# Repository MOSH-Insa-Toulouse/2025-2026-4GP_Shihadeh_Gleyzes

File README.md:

#  Projet : Du capteur au banc de test - Jauge de contrainte en graphite

L'objectif principal de ce projet est d'évaluer une technologie "low-tech" : un capteur de déformation (jauge de contrainte) fabriqué à partir de graphite. Pour cela, nous avons conçu de A à Z une chaîne de mesure complète, allant de la physique du capteur jusqu'à l'application smartphone, en passant par le conditionnement électronique et la création d'un banc de test automatisé.

##  Équipe Projet
* **[Jules Gleyzes]**  **[Samy Shihadeh]**
* Année : 2025-2026

---

##  Sommaire des livrables
1. [Le Capteur en Graphite](#1-le-capteur-en-graphite-low-tech)
2. [Électronique Analogique et Simulation (LTspice)](#2-électronique-analogique-et-simulation-ltspice)
3. [Le Shield PCB (KiCad)](#3-le-shield-pcb-kicad)
4. [Le Code Arduino](#4-programmation-arduino)
5. [L'Application Android](#5-application-android)
6. [Le Banc de Test](#6-le-banc-de-test)
7. [La Datasheet Finale](#7-datasheet-du-capteur)
8. [Conclusion](#8-conclusion)

---

## 1. Le Capteur en Graphite (Low-Tech)
Notre jauge de contrainte a été fabriquée selon une approche "low-tech", en crayonnant simplement une zone spécifique sur une feuille de papier avec un crayon à papier (graphite). Derrière cette apparente simplicité se cache en réalité un capteur régi par la mécanique quantique. 
### 1.1. Géométrie et Fabrication 
**Support :** Papier classique.  **Matériau sensible :** Dépôt de graphite par frottement.  **Dimensions :** Motif en forme de "U" avec une longueur de bande de 35 mm et un espacement de 5 mm.

### 1.2. Principe Physique : 
Réseau de percolation et Effet Tunnel. Les traits de crayon déposés sur du papier forme un **réseau de percolation** : un grand nombre de micro et nano-grains de graphite dispersées de façon aléatoire. Pour que le courant traverse le capteur, les électrons utilisent deux mécanismes : 1. **La conduction ohmique :** Lorsque les grains se touchent physiquement. 2. **L'effet tunnel quantique :** Lorsque deux grains sont séparées par un vide ou un isolant nanométrique, les électrons (qui se comportent comme des ondes) ont une probabilité de "traverser" cette barrière. La résistance électrique liée à cet effet tunnel R_tunnel dépend de manière **exponentielle** de la distance d entre les grains de graphite.
### 1.3. Réponse à la déformation (Macroscopique) 
C'est cette sensibilité exponentielle à la distance nanométrique qui permet au capteur de mesurer une déformation mécanique. **En Tension (étirement / courbure vers l'extérieur) :** Les fibres du papier s'étirent, éloignant les grains de graphite les unes des autres. La distance d des jonctions augmente. L'effet tunnel ne fonctionne plus, ce qui **augmente fortement la résistance électrique globale**. **En Compression (courbure vers l'intérieur) :** Les fibres du papier se resserent. Les grains sont rapprochées, créant de nouveaux contacts physiques et diminuant la distance d des jonctions tunnel. Les électrons circulent beaucoup plus facilement, ce qui **diminue la résistance électrique**. Ce capteur low-tech est donc un détecteur quantique de variations de distances nanométriques.
## 2. Électronique Analogique et Simulation (LTspice)

Avant de passer à la réalisation physique sur notre shield, il est important de valider le comportement de notre signal de manière théorique. Nous avons utilisé le logiciel LTspice pour modéliser le circuit complet afin d'ajuster la valeur de nos composants et vérifier la réponse du système. Notre capteur en graphite possède une résistance électrique très élevée, il ne laisse donc passer qu'un courant de l'ordre du microampère. La carte Arduino ne lisant que des tensions (de 0 à 5V), une amplification du signal est donc essentiel.

### 2.1. Amplification Transimpédance et Étalonnage Dynamique

Le cœur de notre circuit repose sur un amplificateur opérationnel monté en transimpédance. Ce montage force le très faible courant du capteur à traverser la résistance de rétroaction R4 (100 kΩ) pour générer une tension de sortie que l’arduino est capable de lire. 

### 2.2. Filtrage des Parasites Ambiants

Le graphite et les fils de connexion apportent des signaux parasites à cause des ondes ambiantes. Pour obtenir une mesure propre et exploitable, nous avons étagé deux filtres. 

Le premier est un filtre actif formé par le condensateur C2 (1 µF) placé en parallèle de R4. Il crée un filtre passe-bas du premier ordre dont la fréquence de coupure est calculée par la formule f_c = 1/(2pi*R4*C2), ce qui donne environ 1.6 Hz. Cela bloque le bruit à 50 Hz tout en laissant passer les variations lentes correspondant à nos contraintes mécaniques. Enfin, un second filtre passe-bas, passif cette fois, est placé juste avant la broche de lecture de l'Arduino. Composé de R3 (1 kΩ) et C3 (100 nF), il possède une fréquence de coupure d'environ 1.6 kHz pour supprimer les bruits à très haute fréquence.

 **

## 3. Le Shield PCB (KiCad)
 Pour intégrer proprement notre circuit au microcontrôleur, nous avons conçu un "Shield" sur mesure à l'aide du logiciel **KiCad**. Le principe d'un shield est d'être une carte d'extension conçue pour se connecter directement par-dessus la carte Arduino UNO. Cette approche permet de supprimer le câblage pour avoir un tout plus compact et un visuel moins encombré. 
### Les Composants Intégrés 
Notre carte comprend un ensemble d’éléments matériels nécessaires au fonctionnement du système : 
* **Le capteur en graphite **
* **Le circuit d'amplification transimpédance :** Converti le micro-courant du capteur en une tension (0-5V) lisible par la carte arduino et de filtre les bruits parasites. 
* **Le potentiomètre :** Intégré au circuit d'amplification et piloté par la carte, il sert à étalonner le signal. Il adapte le gain en temps réel pour garantir une lecture précise, peu importe la résistance du capteur fabriqué.
* **L'écran OLED :** L'interface visuelle qui permet de lire les mesures en direct et de visualiser les différents menus de la carte. 
* **L'encodeur rotatif :** Molette cliquable permettant à l'utilisateur de naviguer dans les menus de l'écran et de déclencher les mesures. 
* **Le module Bluetooth :** Transmet les données traitées en temps réel vers notre application smartphone Android. 

### De la Conception à la Réalisation 
Pour aboutir à notre carte physique, nous sommes passés par deux grandes étapes de conception sur KiCad : 
**1. Le Schématique Électrique** C'est ici que nous avons défini les liens logiques entre tous nos composants et le microcontrôleur, en utilisant des labels pour garder un document lisible.

**2. Le Routage (PCB)** Une fois le schéma validé, nous avons placé physiquement les composants sur une carte et tracé les pistes de cuivre (en respectant une largeur et une isolation de 0.5 mm minimum).

## 4. Programmation Arduino

Tous les composants de notre shield sont pilotés par une carte Arduino UNO. Le code est disponible dans ce dépôt.

Dès qu'on branche la carte, l'Arduino lance une **calibration automatique**. Le programme va tester rapidement plusieurs valeurs sur le potentiomètre numérique pour s'adapter tout seul à la résistance de votre capteur.

Ensuite, l'écran OLED affiche le menu principal. La navigation se fait très simplement avec l'encodeur rotatif : il suffit de tourner la molette pour faire défiler les menus, et de cliquer dessus pour y entrer.

Le programme propose deux menus :

* **Menu 1 : Mesure en direct** Affiche la résistance du capteur graphite en temps réel. Le code adapte tout seul l'unité (Ohms, kOhms ou MOhms). Pour que l'affichage soit agréable à lire et que les chiffres ne sautent pas dans tous les sens, nous avons ajouté un petit filtre dans le code qui fait une moyenne sur les 15 dernières mesures.

* **Menu 2 : Infos Créateurs**
Un petit menu de crédits qui affiche les informations de notre binôme (Samy Shihadeh & Jules Gleyzes - GP 4A 2026).

## 5. Application Android 

Pour visualiser les données de notre capteur sans avoir besoin d'un ordinateur, nous avons développé une petite application Android. Elle communique directement avec le module Bluetooth de notre carte.

Nous avons créé cette application en utilisant MIT App Inventor qui permet grâce à un système de programmation par blocs de développer rapidement une application fonctionnelle.

L'application a deux rôles principaux :
1. **La connexion :** Elle permet de chercher et de se connecter facilement au module Bluetooth.
3. **L'affichage :** Une fois connectée, elle reçoit les valeurs de résistance mesurées et les affiche sur l'écran du téléphone quand on appuie dessus.

**L'interface utilisateur :**

**Le code par blocs :**

## 6. Le Banc de Test

Pour valider scientifiquement l'efficacité de nos capteurs "low-tech" en graphite, il était indispensable de caractériser leur réponse face à des déformations mécaniques connues. 

Nous avons conçu un banc de test en utilisant une pièce imprimée en 3D en forme de cône. Celui-ci possède différents rayons de courbure de sorte que l’on puisse tordre nos différent de capteurs, fait à partir de différents types de graphite, de la même manière.

Afin d'évaluer et de comparer les performances de nos différents capteurs, nous avons étudié l'évolution de leur signal en fonction de la contrainte mécanique appliquée. Pour ce faire, nous avons tracé la variation relative de la résistance (R - R_0)/R_0 en fonction de la déformation. Avec R la résistance du capteur sous contrainte et R_0 la résistance du capteur lorsqu'il est à plat.

## 7. Datasheet du Capteur

Pour valider le fonctionnement du capteur, nous avons mesuré l'évolution de sa résistance relative (ΔR/R_0) en fonction de la déformation appliquée, en testant différentes duretés de mines de graphite. 

Bien que ces courbes valident le principe physique de base (la résistance augmente en extension et diminue en compression grâce à l'effet tunnel), elles mettent également en évidence les limites du capteur *low-tech* fabriqué à la main :

* **Non-linéarité et variabilité :** L'épaisseur du dépôt de graphite n'étant pas parfaitement uniforme lors d'un coloriage manuel, la réponse électrique présente des irrégularités selon les échantillons.
* **La limite de rupture mécanique :** Sur le graphique de compression, on observe une remontée anormale et soudaine de la résistance pour des déformations supérieures à 0,004. Cela peut s'expliquer par la nature du substrat : au-delà d'un certain angle, le papier ne fait plus que se courber, il peut se casser en marquant un pli. Cette pliure casse physiquement les chemins de percolation du graphite, faussant totalement la mesure.

## 8. Conclusion

Ce projet nous a permis de prouver qu'il est possible de créer un capteur de flexion fonctionnel avec un simple crayon à papier. 

Le comportement du capteur dépend directement de la composition de la mine, qui est un mélange de **graphite** (conducteur) et **d'argile** (isolant) :

* **Les mines grasses (ex: 3B) :** Riches en graphite, elles déposent une couche épaisse et très conductrice sur le papier.Le capteur est donc **stable et linéaire, mais moins sensible**.
* **Les mines dures (ex: 3H) :** Riches en argile (isolante) et pauvres en graphite, elles laissent un dépôt plus fin. À la moindre déformation, ce fragile réseau conducteur risque de se rompre partiellement. Le capteur devient alors **extrêmement sensible**, mais ses mesures sont plus difficiles à répéter.
On a pu voir que plus la mine du crayon est dure, plus le capteur réagit fort. Cependant, les mines classiques (HB, 2B) offrent des mesures plus stables.

### Peut-on industrialiser ce capteur ?
À grande échelle, **non**. Le principal problème est qu'il est impossible de colorier deux capteurs exactement de la même manière à la main. Les résultats sont donc trop variables pour l'industrie. De plus, les tests réalisés sur les capteur ont démontré leurs manque de duraibilité, les morceaux de papier se cassent après peu d'utilisations.

Précision après présentation :

La qualité de nos mesure ne permet pas de s'exprimer clairement sur la possibilité d'industrialiser ce capteur, cependant notre capteur a très basse compression ou extension démontre une sensibilité extremement bonne (par exemple nous avons presque une sensibilité de 100 pour le crayon B en compression) ce qui nous laisse a penser qu'après stabilisation des mesures avec des modifications apportées sur nos capteurs, ils pourraient avoir des caractéristiques interessantes d'un point de vu performance.

Une piste possible serait d'appliquer de la lacque ou encore de chauffer nos capteur avant test pour bien fixer le graphite sur notre feuille et refaire nos mesures pour déterminer si nos capteurs se comportent normalement.

De plus, son coût quasi nul et sa simplicité de fabrication en font un très bon outil éducatif qui permettent de découvrir tout les aspects nécessaire à prendre en compte et à étudier dans la création d'un capteur.

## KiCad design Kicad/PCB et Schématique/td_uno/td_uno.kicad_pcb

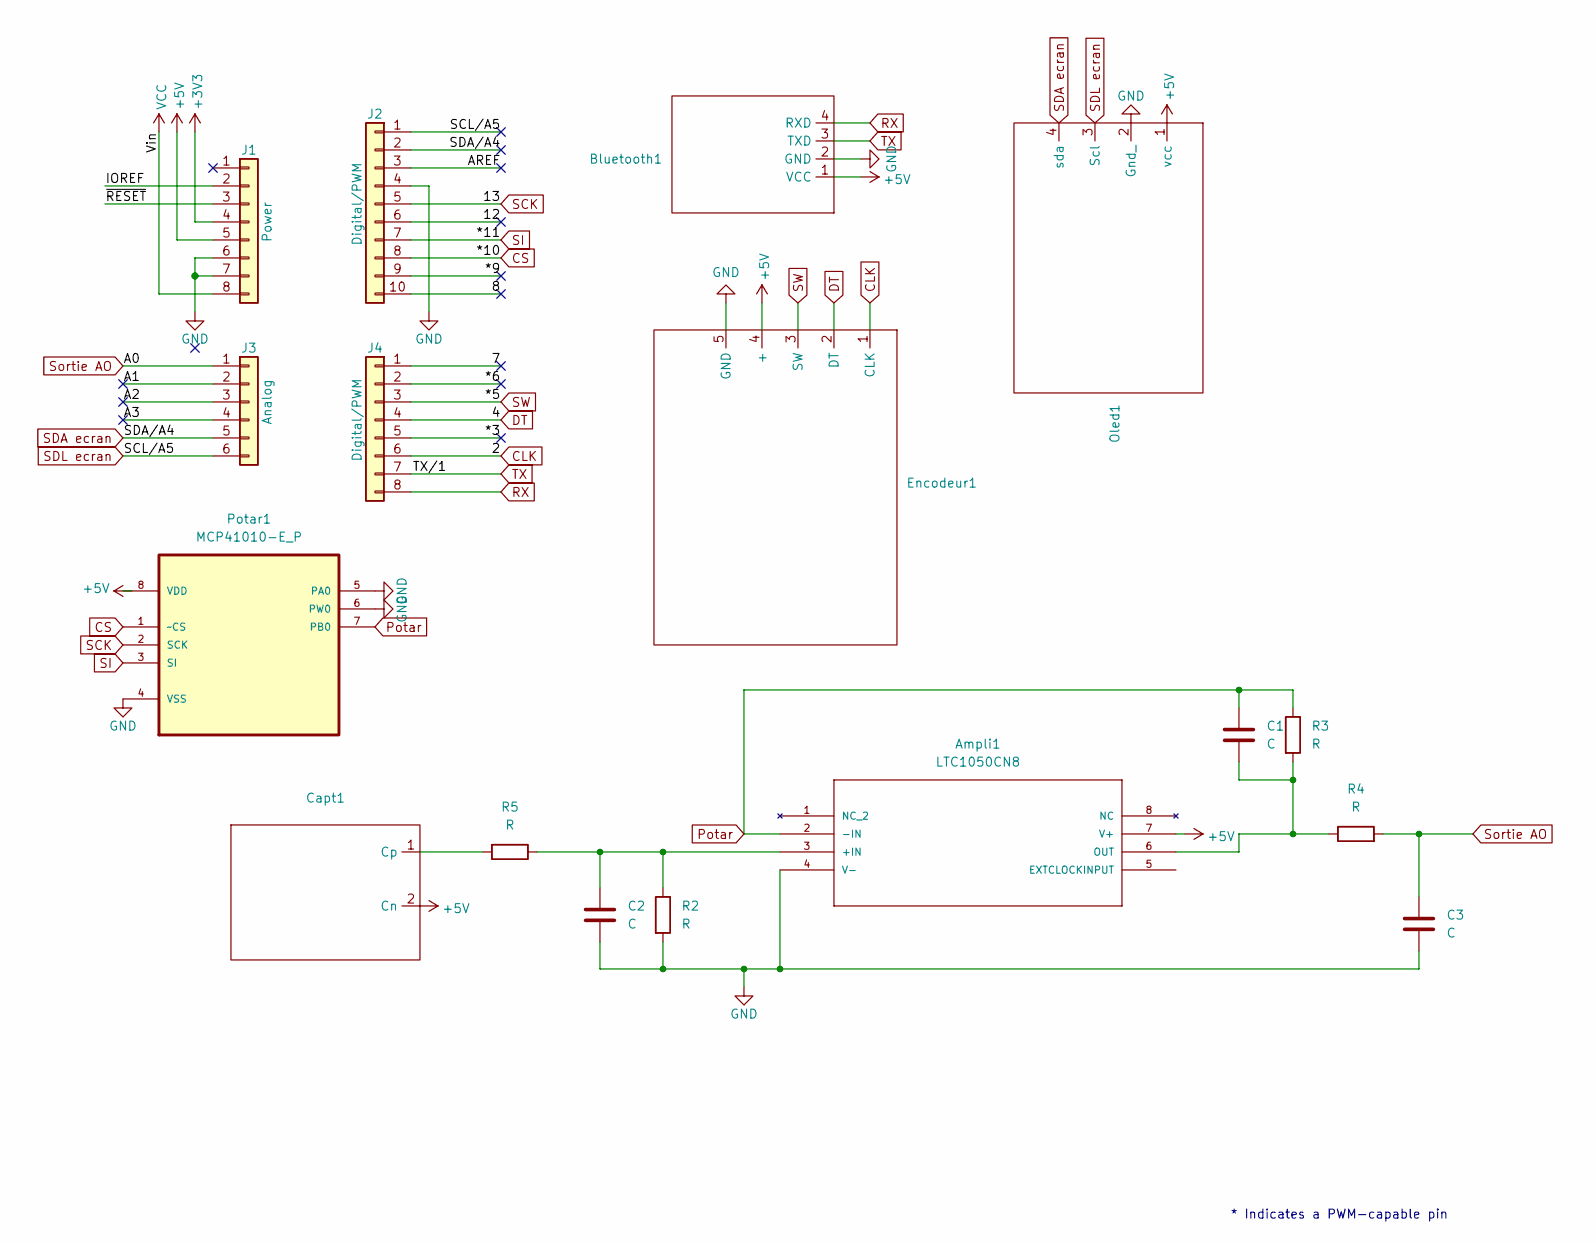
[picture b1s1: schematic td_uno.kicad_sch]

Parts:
Ampli1: LTC1050CN8; Ampli; MANUFACTURER_PART_NUMBER ltc1050cn8
Bluetooth1: Bluetooth
C1, C2, C3: C; C_Disc_D4.3mm_W1.9mm_P5.00mm
Capt1: Capt
Encodeur1: Encodeur
J1: Power; PinSocket_1x08_P2.54mm_Vertical
J2: Digital/PWM; PinSocket_1x10_P2.54mm_Vertical
J3: Analog; PinSocket_1x06_P2.54mm_Vertical
J4: Digital/PWM; PinSocket_1x08_P2.54mm_Vertical
Oled1: Oled
Potar1: MCP41010-E_P; Potar; MPN MCP41010-E/P; DigiKey_Part_Number MCP41010-E/P-ND
R2, R3, R4, R5: R; R_Axial_DIN0204_L3.6mm_D1.6mm_P5.08mm_Horizontal

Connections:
+3V3: J1.4
+5V: Ampli1.7 (V+), Bluetooth1.1 (VCC), Capt1.2 (Cn), Encodeur1.4 (+), J1.5, Oled1.1 (vcc), Potar1.8 (VDD)
/7: J4.1
/8: J2.10
/12: J2.6
/*3: J4.5
/*6: J4.2
/*9: J2.9
/A1: J3.2
/A2: J3.3
/A3: J3.4
/AREF: J2.3
/IOREF: J1.2
/~RESET: J1.3
CLK: Encodeur1.1 (CLK), J4.6
CS: J2.8, Potar1.1 (~CS)
DT: Encodeur1.2 (DT), J4.4
GND: Ampli1.4 (V-), Bluetooth1.2 (GND), C2.2, C3.2, Encodeur1.5 (GND), J1.6, J1.7, J2.4, Oled1.2 (Gnd_), Potar1.4 (VSS), Potar1.5 (PA0), Potar1.6 (PW0), R2.2
unnamed: Ampli1.3 (+IN), C2.1, R2.1, R5.1
unnamed: Ampli1.6 (OUT), C1.2, R3.2, R4.1
unnamed: Capt1.1 (Cp), R5.2
Potar: Ampli1.2 (-IN), C1.1, Potar1.7 (PB0), R3.1
RX: Bluetooth1.4 (RXD), J4.8
SCK: J2.5, Potar1.2 (SCK)
SDA ecran: J2.2, J3.5, Oled1.4 (sda)
SDL ecran: J2.1, J3.6, Oled1.3 (Scl)
SI: J2.7, Potar1.3 (SI)
SW: Encodeur1.3 (SW), J4.3
Sortie AO: C3.1, J3.1, R4.2
TX: Bluetooth1.3 (TXD), J4.7
VCC: J1.8

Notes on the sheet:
* Indicates a PWM-capable pin

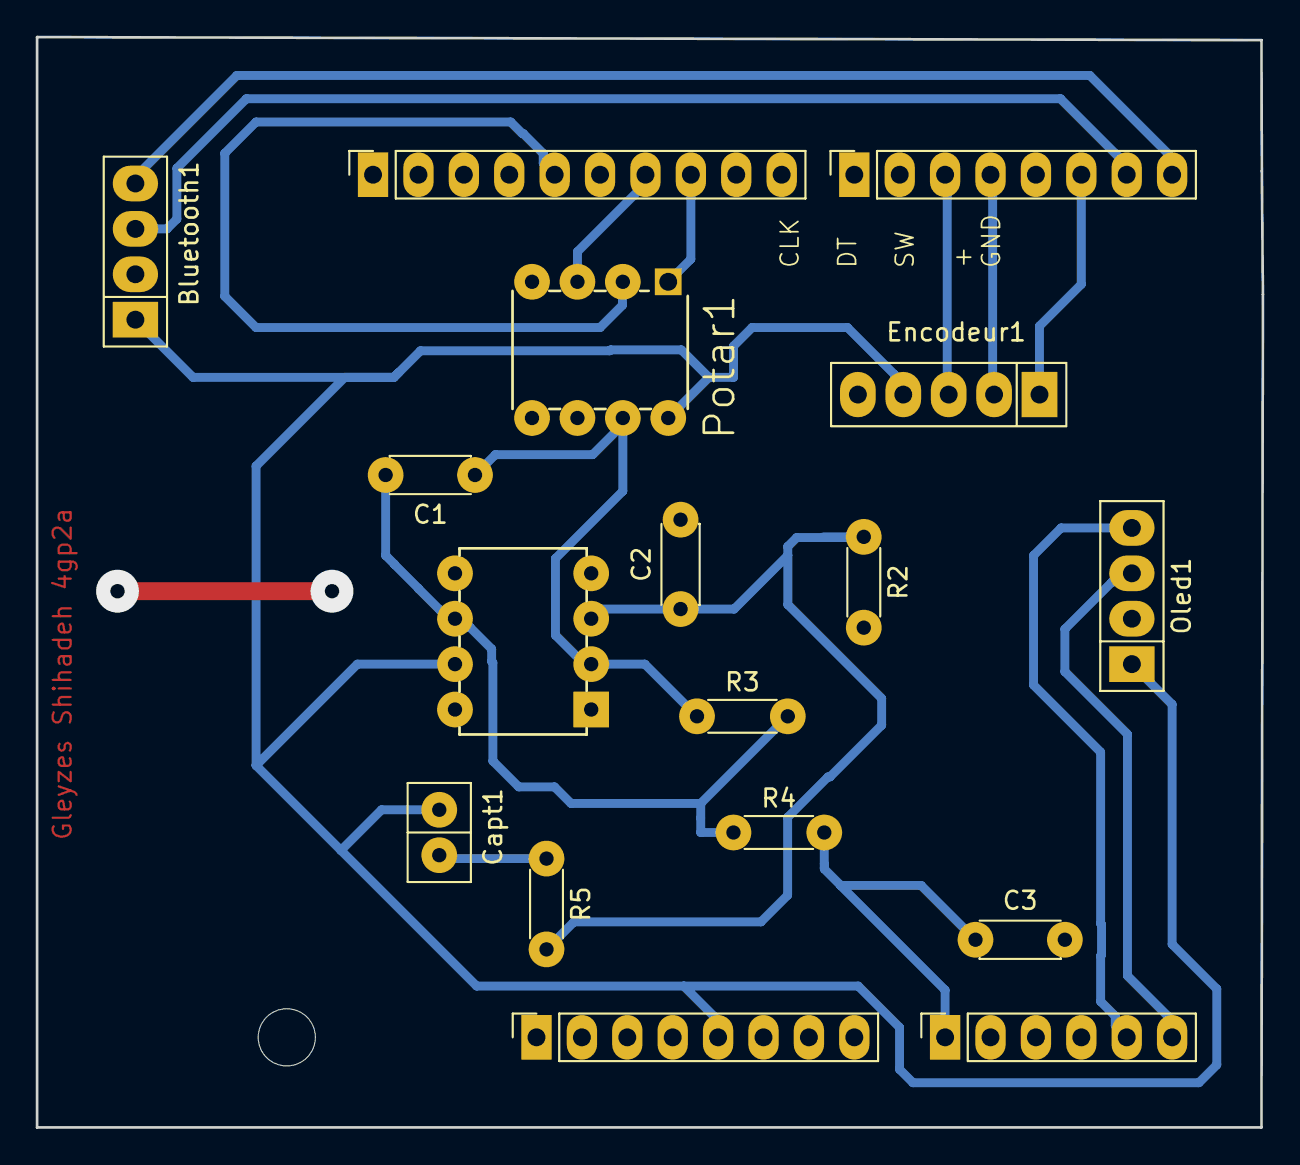
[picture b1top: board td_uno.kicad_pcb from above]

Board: 2 copper layers, 68.6 x 61.0 mm, 18 parts (0 on the bottom side), 17 nets.

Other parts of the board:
MH2: MountingHole_3.2mm

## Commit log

2026-02-13 Create test
    test
2026-04-09 Add project title and year to README
2026-04-09 Update project title and add summary section
2026-04-09 Enhance README with sensor operation details
    Added detailed explanation of the percolation network and tunneling effect in the sensor's operation, including its response to mechanical deformation.
2026-04-11 Update README with clearer description of concepts
    Clarified the explanation of the percolation network and quantum tunneling effect in the README.
2026-04-13 Add Arduino code section to README
    Added Arduino code section with functionality details and menu descriptions.
2026-04-13 Fix link text for Arduino code section in README
2026-04-13 Remove general operation and interface sections from README
    Removed sections about general operation and screen interface from the README.
2026-04-15 Expand sensor datasheet with performance analysis
    Added detailed analysis of sensor performance and limitations based on resistance measurements. Discussed the impact of graphite hardness on sensor sensitivity and durability.

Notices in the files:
parts and their libraries:
COPYRIGHT: Copyright C 2016 Accelerated Designs. All rights reserved
